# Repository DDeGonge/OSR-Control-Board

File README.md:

# OSR-Control-Board
Open Source Robotics Control Board - The cheap, overpowered, easy to use robotics controller.

## BOM
Latest BOM can be found [here](https://octopart.com/bom-tool/g8IoScnJ)

## Bootloader
Flashing instructions are found [here](https://learn.adafruit.com/how-to-program-samd-bootloaders/programming-the-bootloader-with-atmel-studio). Follow directions for Feather M4. Notch on flex cable faces AWAY from mcu.

## Random Stuff
Generate MD5 sum for packages - `CertUtil -hashfile C:\TEMP\MyDataFile.img MD5`

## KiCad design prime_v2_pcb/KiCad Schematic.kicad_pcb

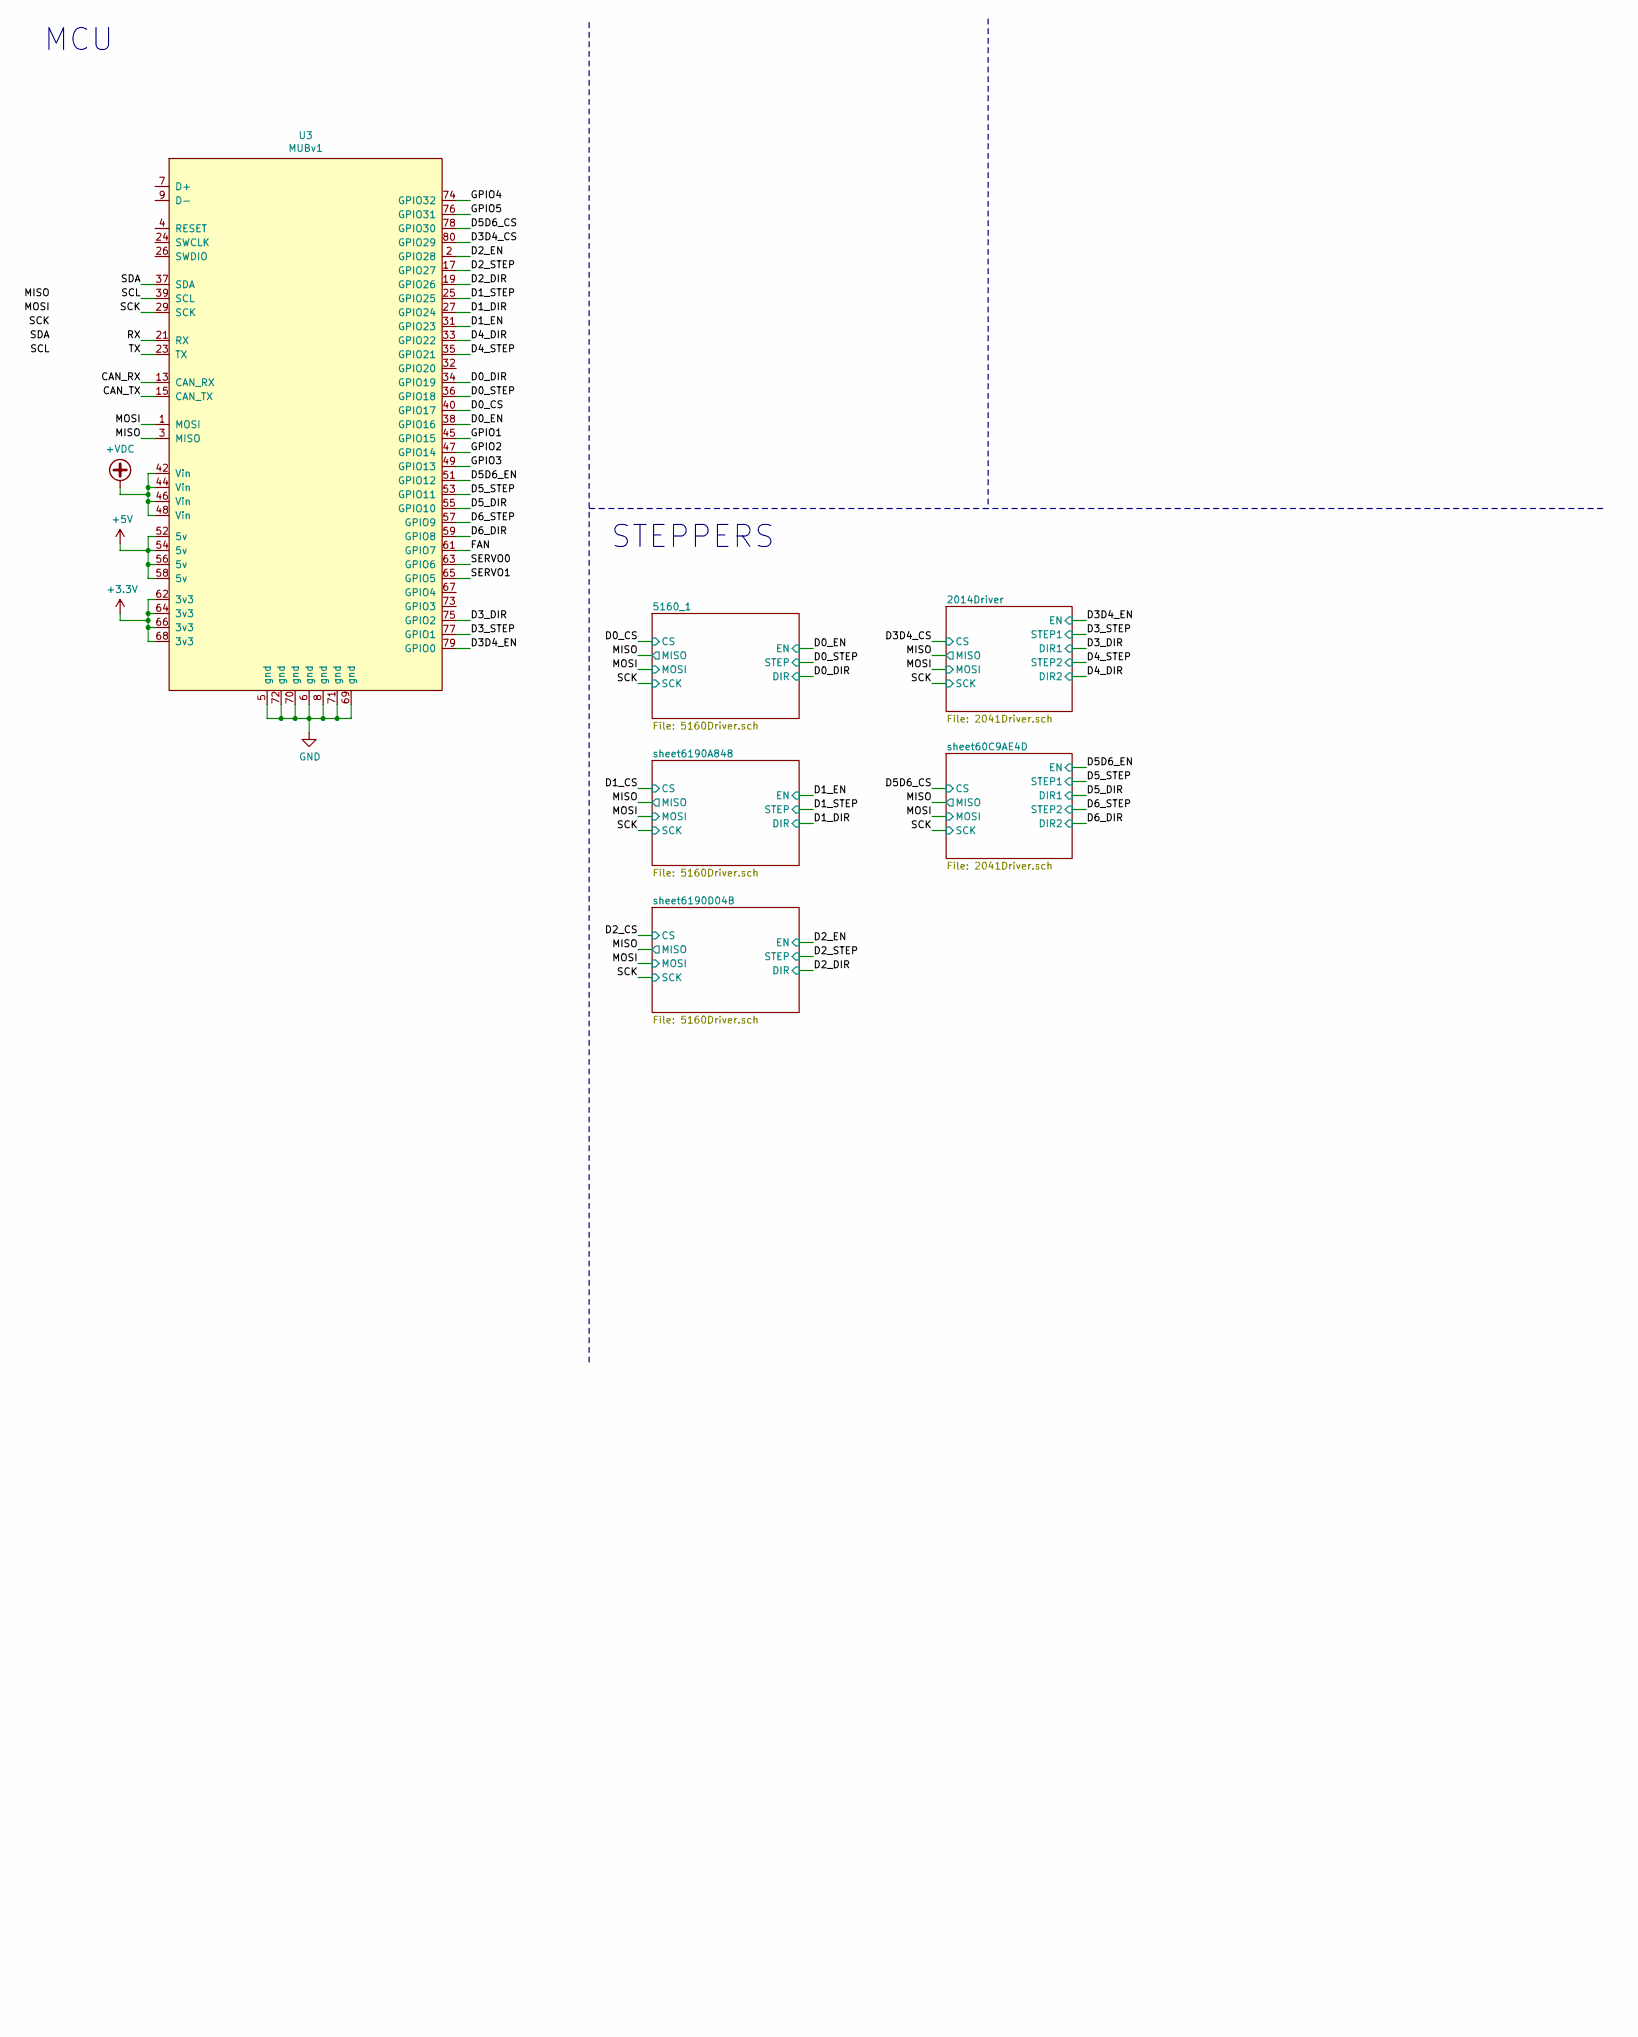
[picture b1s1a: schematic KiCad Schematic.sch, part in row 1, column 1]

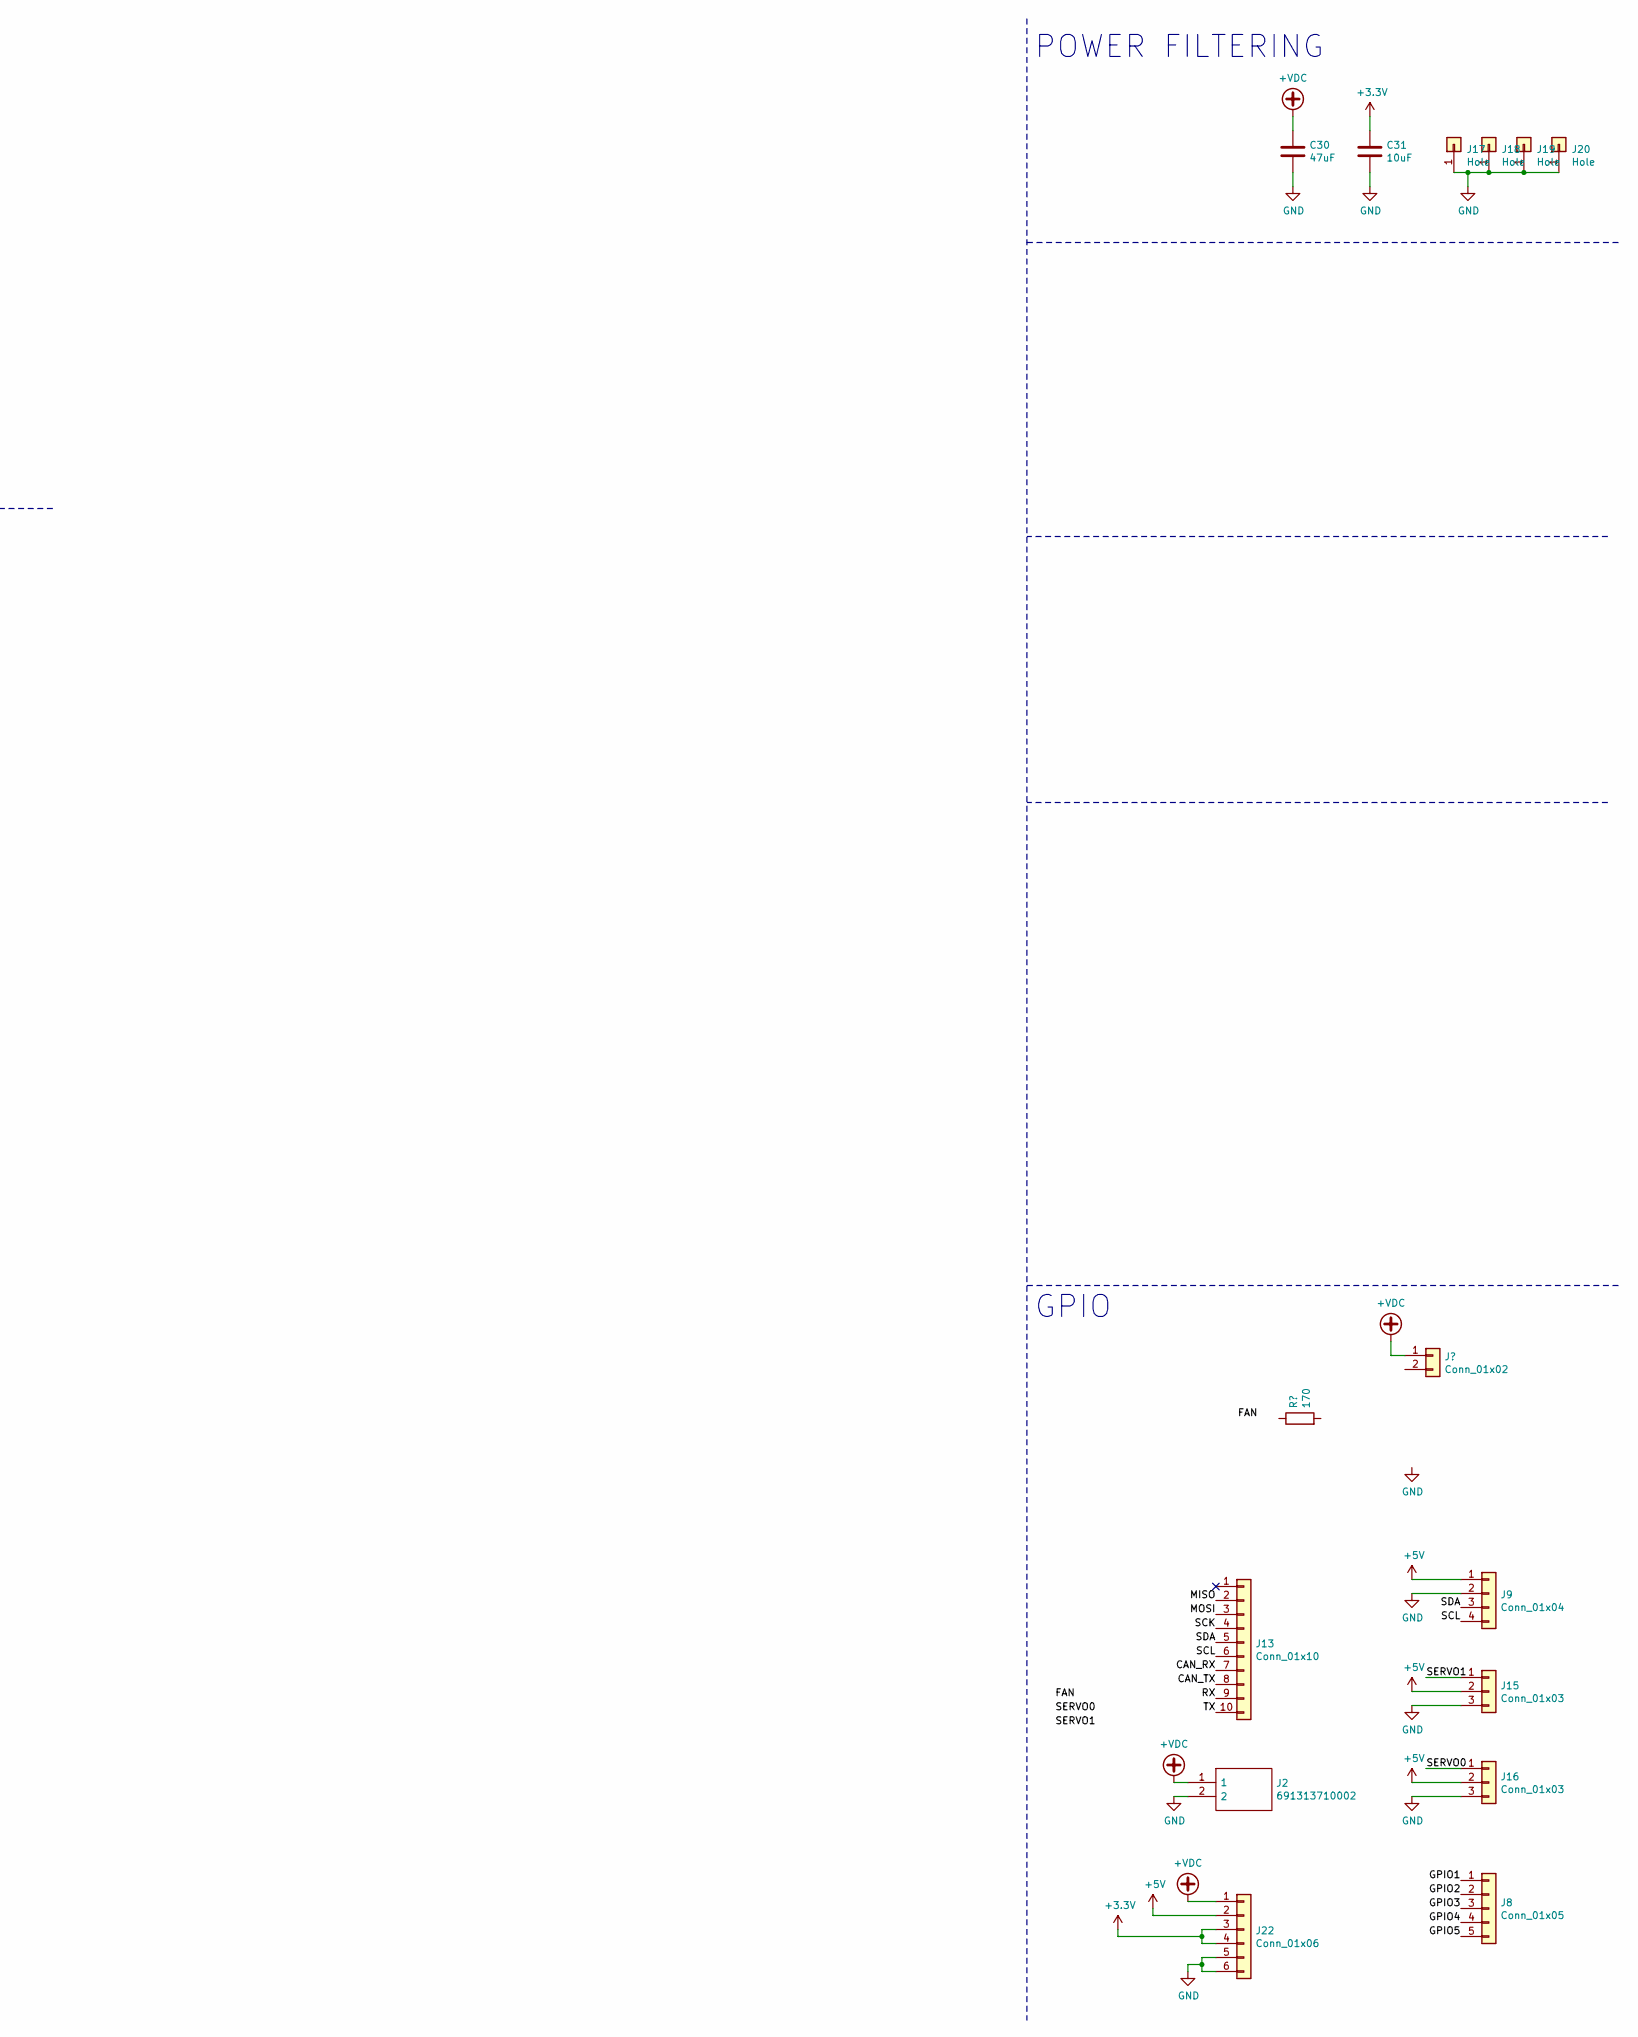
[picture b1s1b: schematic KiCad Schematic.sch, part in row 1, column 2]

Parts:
C30: 47uF; CP_Elec_6.3x7.7
C31: 10uF; C_0805_2012Metric
J2: 691313710002; Mouser Part Number 710-691313710002
J8: Conn_01x05; PinHeader_1x05_P2.54mm_Vertical
J9: Conn_01x04; PinHeader_1x04_P2.54mm_Vertical
J13: Conn_01x10; PinHeader_1x10_P2.54mm_Vertical
J15, J16: Conn_01x03; PinHeader_1x03_P2.54mm_Vertical
J17, J18, J19, J20: Hole; MountingHole_2.7mm_M2.5_DIN965_Pad
J22: Conn_01x06; PinSocket_1x06_P2.54mm_Vertical
U3: MUBv1; MUB_v1

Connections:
+5V: J9.1, J15.2, J16.2, J22.2, U3.52 (5v), U3.54 (5v), U3.56 (5v), U3.58 (5v)
+VDC: C30.1, J2.1, J22.1, U3.42 (Vin), U3.44 (Vin), U3.46 (Vin), U3.48 (Vin); also elsewhere on the board
/CAN_RX: J13.7, U3.13 (CAN_RX)
/CAN_TX: J13.8, U3.15 (CAN_TX)
/D0_CS: U3.40 (GPIO17); also elsewhere on the board
/D0_DIR: U3.34 (GPIO19); also elsewhere on the board
/D0_EN: U3.38 (GPIO16); also elsewhere on the board
/D0_STEP: U3.36 (GPIO18); also elsewhere on the board
/D1_DIR: U3.27 (GPIO24); also elsewhere on the board
/D1_EN: U3.31 (GPIO23); also elsewhere on the board
/D1_STEP: U3.25 (GPIO25); also elsewhere on the board
/D2_DIR: U3.19 (GPIO26); also elsewhere on the board
/D2_EN: U3.2 (GPIO28); also elsewhere on the board
/D2_STEP: U3.17 (GPIO27); also elsewhere on the board
/D3D4_CS: U3.80 (GPIO29); also elsewhere on the board
/D3D4_EN: U3.79 (GPIO0); also elsewhere on the board
/D3_DIR: U3.75 (GPIO2); also elsewhere on the board
/D3_STEP: U3.77 (GPIO1); also elsewhere on the board
/D4_DIR: U3.33 (GPIO22); also elsewhere on the board
/D4_STEP: U3.35 (GPIO21); also elsewhere on the board
/D5D6_CS: U3.78 (GPIO30); also elsewhere on the board
/D5D6_EN: U3.51 (GPIO12); also elsewhere on the board
/D5_DIR: U3.55 (GPIO10); also elsewhere on the board
/D5_STEP: U3.53 (GPIO11); also elsewhere on the board
/D6_DIR: U3.59 (GPIO8); also elsewhere on the board
/D6_STEP: U3.57 (GPIO9); also elsewhere on the board
/GPIO1: J8.1, U3.45 (GPIO15)
/GPIO2: J8.2, U3.47 (GPIO14)
/GPIO3: J8.3, U3.49 (GPIO13)
/GPIO4: J8.4, U3.74 (GPIO32)
/GPIO5: J8.5, U3.76 (GPIO31)
/MISO: J13.2, U3.3 (MISO); also elsewhere on the board
/MOSI: J13.3, U3.1 (MOSI); also elsewhere on the board
/RX: J13.9, U3.21 (RX)
/SCK: J13.4, U3.29 (SCK); also elsewhere on the board
/SCL: J9.4, J13.6, U3.39 (SCL)
/SDA: J9.3, J13.5, U3.37 (SDA)
/TX: J13.10, U3.23 (TX)
GND: C30.2, C31.2, J2.2, J9.2, J15.3, J16.3, J17.1, J18.1, J19.1, J20.1, J22.5, J22.6, U3.5 (gnd), U3.6 (gnd), U3.8 (gnd), U3.69 (gnd), U3.70 (gnd), U3.71 (gnd), U3.72 (gnd); also elsewhere on the board

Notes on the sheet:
GPIO
POWER FILTERING
MCU
STEPPERS

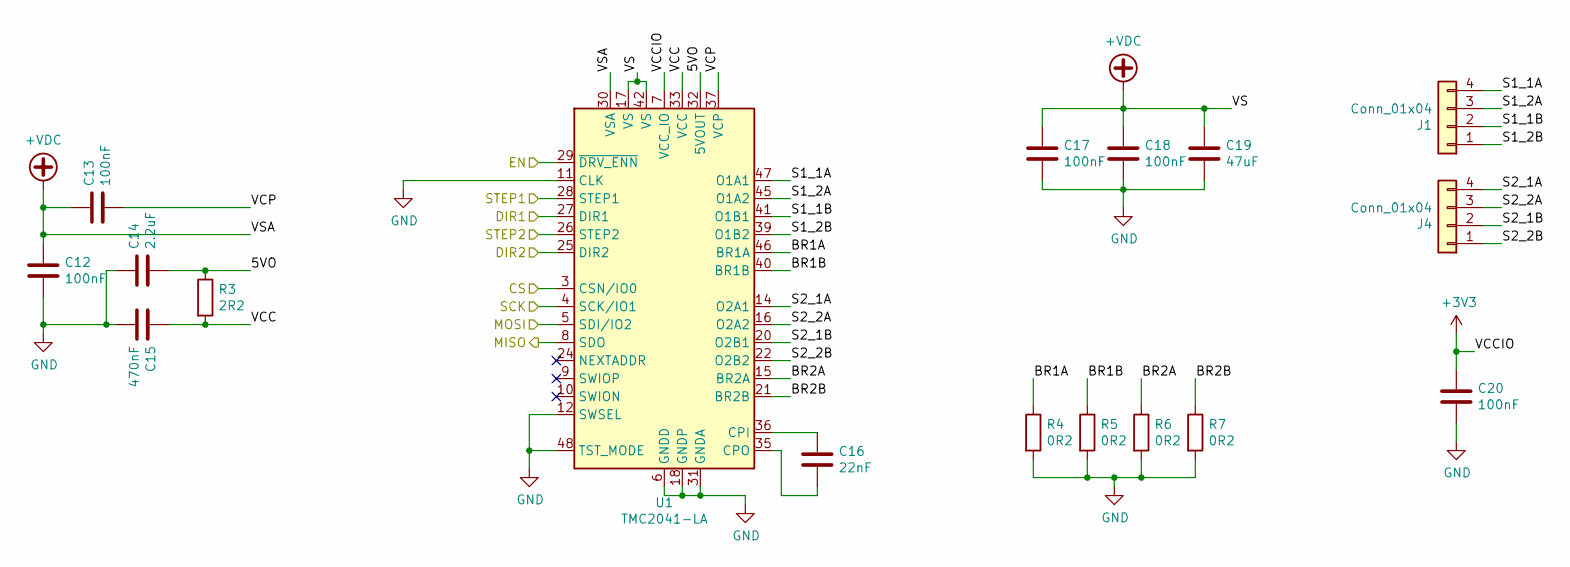
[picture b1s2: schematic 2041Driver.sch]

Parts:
C12, C13, C17, C18, C20: 100nF; C_0603_1608Metric
C14: 2.2uF; C_1206_3216Metric
C15: 470nF; C_0603_1608Metric
C16: 22nF; C_0603_1608Metric
C19: 47uF; CP_Elec_6.3x7.7
J1, J4: Conn_01x04; PinHeader_1x04_P2.54mm_Vertical
R3: 2R2; R_0603_1608Metric
R4, R5, R6, R7: 0R2; R_0805_2012Metric
U1: TMC2041-LA; QFN-48-1EP_7x7mm_P0.5mm_EP5.3x5.3mm

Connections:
+VDC: C12.1, C13.1, C17.1, C18.1, C19.1, U1.17 (VS), U1.19 (VS), U1.30 (VSA), U1.42 (VS), U1.44 (VS); also elsewhere on the board
/2014Driver/5VO: C14.2, R3.1, U1.32 (5VOUT)
/2014Driver/BR1A: R4.1, U1.46 (BR1A)
/2014Driver/BR1B: R5.1, U1.40 (BR1B)
/2014Driver/BR2A: R6.1, U1.15 (BR2A)
/2014Driver/BR2B: R7.1, U1.21 (BR2B)
/2014Driver/S1_1A: J1.4, U1.47 (O1A1)
/2014Driver/S1_1B: J1.2, U1.41 (O1B1)
/2014Driver/S1_2A: J1.3, U1.45 (O1A2)
/2014Driver/S1_2B: J1.1, U1.39 (O1B2)
/2014Driver/S2_1A: J4.4, U1.14 (O2A1)
/2014Driver/S2_1B: J4.2, U1.20 (O2B1)
/2014Driver/S2_2A: J4.3, U1.16 (O2A2)
/2014Driver/S2_2B: J4.1, U1.22 (O2B2)
/2014Driver/VCC: C15.1, R3.2, U1.33 (VCC)
/2014Driver/VCP: C13.2, U1.37 (VCP)
/D3D4_CS: U1.3 (CSN/IO0); also elsewhere on the board
/D3D4_EN: U1.29 (~DRV_ENN); also elsewhere on the board
/D3_DIR: U1.27 (DIR1); also elsewhere on the board
/D3_STEP: U1.28 (STEP1); also elsewhere on the board
/D4_DIR: U1.25 (DIR2); also elsewhere on the board
/D4_STEP: U1.26 (STEP2); also elsewhere on the board
/MISO: U1.8 (SDO); also elsewhere on the board
/MOSI: U1.5 (SDI/IO2); also elsewhere on the board
/SCK: U1.4 (SCK/IO1); also elsewhere on the board
GND: C12.2, C14.1, C15.2, C17.2, C18.2, C19.2, C20.2, R4.2, R5.2, R6.2, R7.2, U1.1 (GNDD), U1.2 (GNDD), U1.6 (GNDD), U1.11 (CLK), U1.12 (SWSEL), U1.13 (GNDD), U1.18 (GNDP), U1.23 (GNDD), U1.31 (GNDA), U1.34 (GNDD), U1.38 (GNDD), U1.43 (GNDP), U1.48 (TST_MODE), U1.49 (GNDD); also elsewhere on the board
unnamed: C16.1, U1.36 (CPI)
unnamed: C16.2, U1.35 (CPO)

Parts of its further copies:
C21, C22, C27, C42, C50: 100nF; C_0603_1608Metric
C23: 2.2uF; C_1206_3216Metric
C24: 470nF; C_0603_1608Metric
C26: 22nF; C_0603_1608Metric
C49: 47uF; CP_Elec_6.3x7.7
J5, J7: Conn_01x04; PinHeader_1x04_P2.54mm_Vertical
R8: 2R2; R_0603_1608Metric
R9, R10, R11, R12: 0R2; R_0805_2012Metric
U2: TMC2041-LA; QFN-48-1EP_7x7mm_P0.5mm_EP5.3x5.3mm

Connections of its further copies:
+VDC: C21.1, C22.1, C27.1, C42.1, C49.1, U2.17 (VS), U2.19 (VS), U2.30 (VSA), U2.42 (VS), U2.44 (VS); also elsewhere on the board
/D5D6_CS: U2.3 (CSN/IO0); also elsewhere on the board
/D5D6_EN: U2.29 (~DRV_ENN); also elsewhere on the board
/D5_DIR: U2.27 (DIR1); also elsewhere on the board
/D5_STEP: U2.28 (STEP1); also elsewhere on the board
/D6_DIR: U2.25 (DIR2); also elsewhere on the board
/D6_STEP: U2.26 (STEP2); also elsewhere on the board
/MISO: U2.8 (SDO); also elsewhere on the board
/MOSI: U2.5 (SDI/IO2); also elsewhere on the board
/SCK: U2.4 (SCK/IO1); also elsewhere on the board
/sheet60C9AE4D/5VO: C23.2, R8.1, U2.32 (5VOUT)
/sheet60C9AE4D/BR1A: R9.1, U2.46 (BR1A)
/sheet60C9AE4D/BR1B: R10.1, U2.40 (BR1B)
/sheet60C9AE4D/BR2A: R11.1, U2.15 (BR2A)
/sheet60C9AE4D/BR2B: R12.1, U2.21 (BR2B)
/sheet60C9AE4D/S1_1A: J5.4, U2.47 (O1A1)
/sheet60C9AE4D/S1_1B: J5.2, U2.41 (O1B1)
/sheet60C9AE4D/S1_2A: J5.3, U2.45 (O1A2)
/sheet60C9AE4D/S1_2B: J5.1, U2.39 (O1B2)
/sheet60C9AE4D/S2_1A: J7.4, U2.14 (O2A1)
/sheet60C9AE4D/S2_1B: J7.2, U2.20 (O2B1)
/sheet60C9AE4D/S2_2A: J7.3, U2.16 (O2A2)
/sheet60C9AE4D/S2_2B: J7.1, U2.22 (O2B2)
/sheet60C9AE4D/VCC: C24.1, R8.2, U2.33 (VCC)
/sheet60C9AE4D/VCP: C22.2, U2.37 (VCP)
GND: C21.2, C23.1, C24.2, C27.2, C42.2, C49.2, C50.2, R9.2, R10.2, R11.2, R12.2, U2.1 (GNDD), U2.2 (GNDD), U2.6 (GNDD), U2.11 (CLK), U2.12 (SWSEL), U2.13 (GNDD), U2.18 (GNDP), U2.23 (GNDD), U2.31 (GNDA), U2.34 (GNDD), U2.38 (GNDD), U2.43 (GNDP), U2.48 (TST_MODE), U2.49 (GNDD); also elsewhere on the board
unnamed: C26.1, U2.36 (CPI)
unnamed: C26.2, U2.35 (CPO)

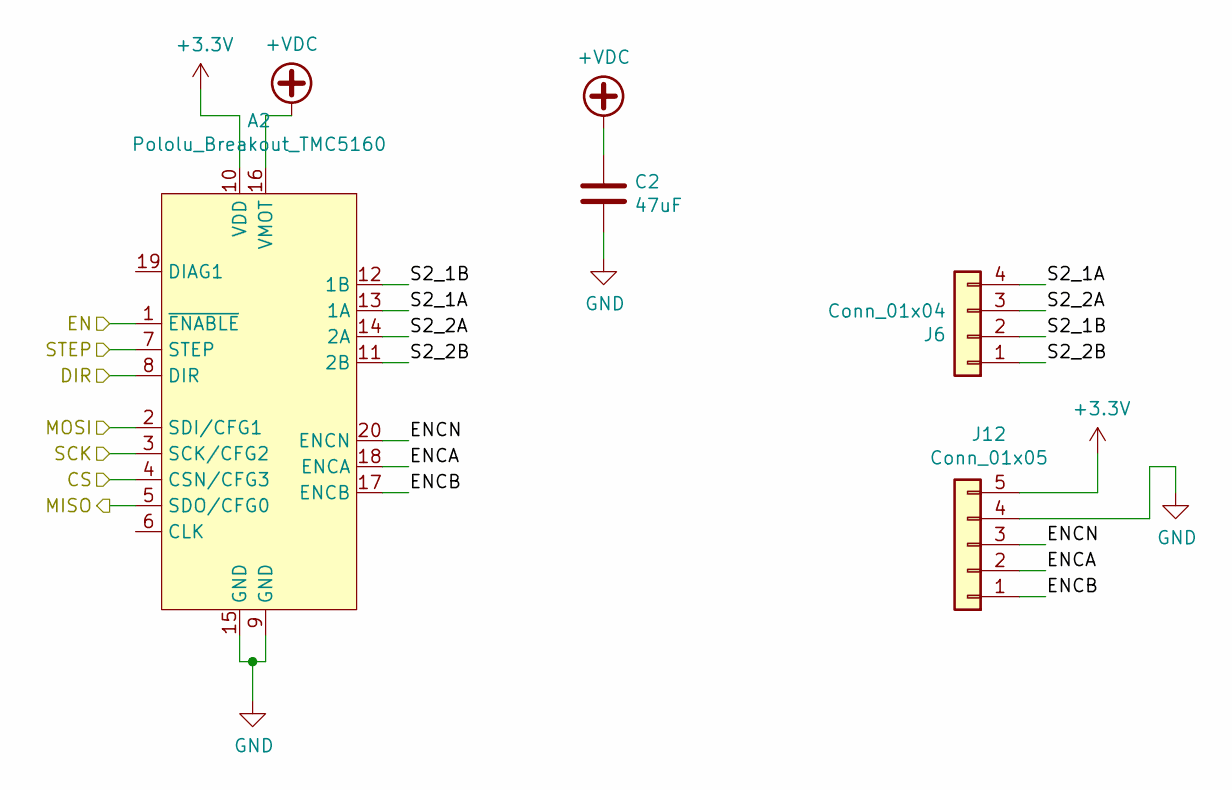
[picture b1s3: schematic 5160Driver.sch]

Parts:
A1: Pololu_Breakout_TMC5160; Pololu_Breakout-20_15.2x20.3mm
C1: 47uF; CP_Elec_6.3x7.7
J3: Conn_01x04; PinHeader_1x04_P2.54mm_Vertical
J11: Conn_01x05; PinHeader_1x05_P2.54mm_Vertical

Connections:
+VDC: A1.16 (VMOT), C1.1; also elsewhere on the board
/5160_1/ENCA: A1.18 (ENCA), J11.2
/5160_1/ENCB: A1.17 (ENCB), J11.1
/5160_1/ENCN: A1.20 (ENCN), J11.3
/5160_1/S2_1A: A1.13 (1A), J3.4
/5160_1/S2_1B: A1.12 (1B), J3.2
/5160_1/S2_2A: A1.14 (2A), J3.3
/5160_1/S2_2B: A1.11 (2B), J3.1
/D0_CS: A1.4 (CSN/CFG3); also elsewhere on the board
/D0_DIR: A1.8 (DIR); also elsewhere on the board
/D0_EN: A1.1 (~ENABLE); also elsewhere on the board
/D0_STEP: A1.7 (STEP); also elsewhere on the board
/MISO: A1.5 (SDO/CFG0); also elsewhere on the board
/MOSI: A1.2 (SDI/CFG1); also elsewhere on the board
/SCK: A1.3 (SCK/CFG2); also elsewhere on the board
GND: A1.9 (GND), A1.15 (GND), C1.2, J11.4; also elsewhere on the board

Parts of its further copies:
A2, A3: Pololu_Breakout_TMC5160; Pololu_Breakout-20_15.2x20.3mm
C2, C3: 47uF; CP_Elec_6.3x7.7
J6, J10: Conn_01x04; PinHeader_1x04_P2.54mm_Vertical
J12, J14: Conn_01x05; PinHeader_1x05_P2.54mm_Vertical

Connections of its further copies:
+VDC: A2.16 (VMOT), A3.16 (VMOT), C2.1, C3.1; also elsewhere on the board
/D1_CS: A2.4 (CSN/CFG3)
/D1_DIR: A2.8 (DIR); also elsewhere on the board
/D1_EN: A2.1 (~ENABLE); also elsewhere on the board
/D1_STEP: A2.7 (STEP); also elsewhere on the board
/D2_CS: A3.4 (CSN/CFG3)
/D2_DIR: A3.8 (DIR); also elsewhere on the board
/D2_EN: A3.1 (~ENABLE); also elsewhere on the board
/D2_STEP: A3.7 (STEP); also elsewhere on the board
/MISO: A2.5 (SDO/CFG0), A3.5 (SDO/CFG0); also elsewhere on the board
/MOSI: A2.2 (SDI/CFG1), A3.2 (SDI/CFG1); also elsewhere on the board
/SCK: A2.3 (SCK/CFG2), A3.3 (SCK/CFG2); also elsewhere on the board
/sheet6190A848/ENCA: A2.18 (ENCA), J12.2
/sheet6190A848/ENCB: A2.17 (ENCB), J12.1
/sheet6190A848/ENCN: A2.20 (ENCN), J12.3
/sheet6190A848/S2_1A: A2.13 (1A), J6.4
/sheet6190A848/S2_1B: A2.12 (1B), J6.2
/sheet6190A848/S2_2A: A2.14 (2A), J6.3
/sheet6190A848/S2_2B: A2.11 (2B), J6.1
/sheet6190D04B/ENCA: A3.18 (ENCA), J14.2
/sheet6190D04B/ENCB: A3.17 (ENCB), J14.1
/sheet6190D04B/ENCN: A3.20 (ENCN), J14.3
/sheet6190D04B/S2_1A: A3.13 (1A), J10.4
/sheet6190D04B/S2_1B: A3.12 (1B), J10.2
/sheet6190D04B/S2_2A: A3.14 (2A), J10.3
/sheet6190D04B/S2_2B: A3.11 (2B), J10.1
GND: A2.9 (GND), A2.15 (GND), A3.9 (GND), A3.15 (GND), C2.2, C3.2, J12.4, J14.4; also elsewhere on the board

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
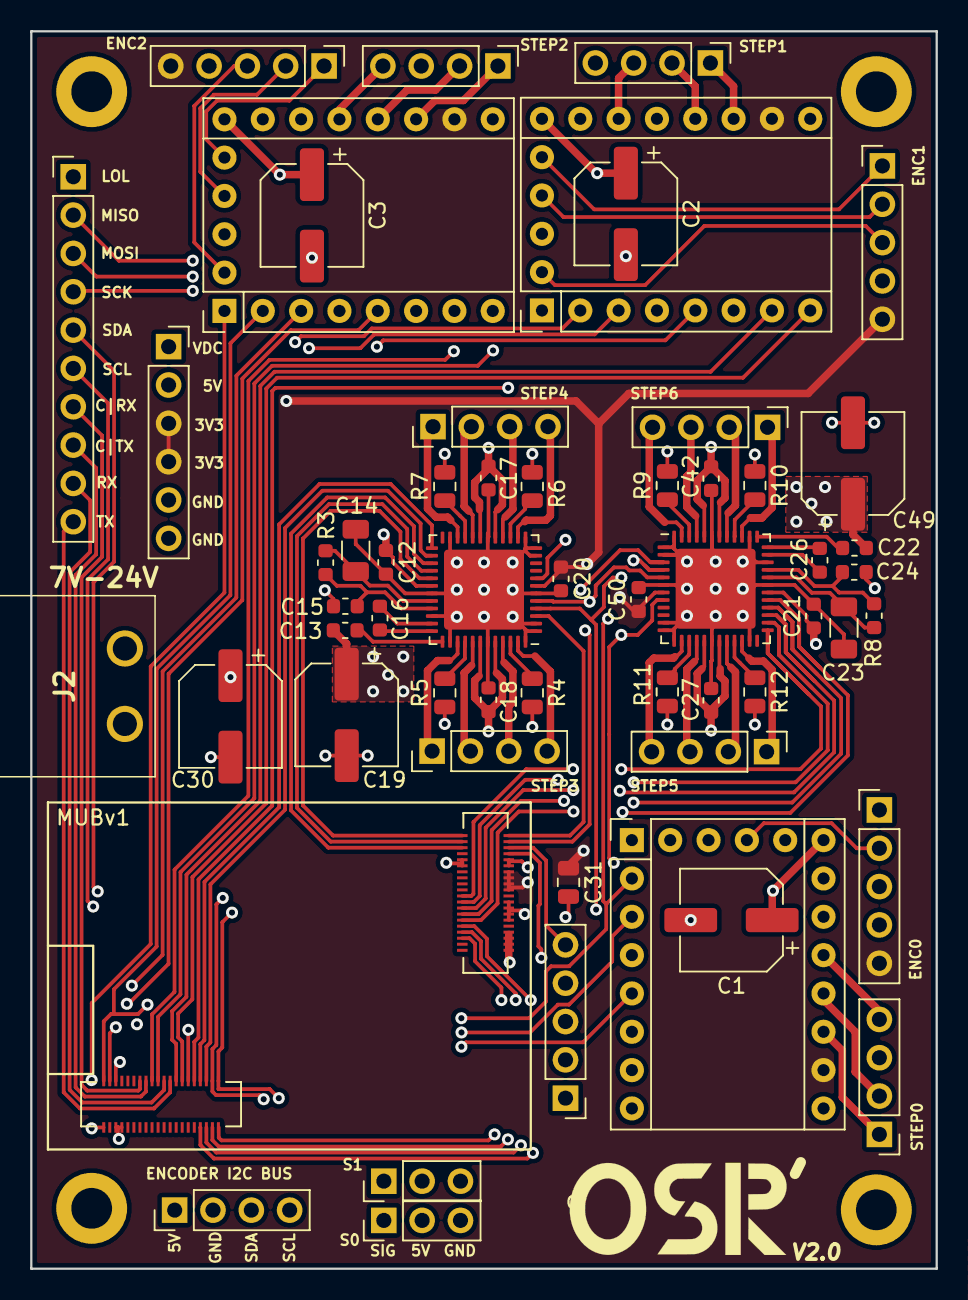
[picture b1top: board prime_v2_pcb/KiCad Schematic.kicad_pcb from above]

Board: 4 copper layers, 60.0 x 82.0 mm, 60 parts (0 on the bottom side), 95 nets.

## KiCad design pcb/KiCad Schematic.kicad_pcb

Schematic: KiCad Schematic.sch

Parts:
C1, C3, C5, C6, C7, C8, C9, C10, C11: 1uF; C_0603_1608Metric
C2, C31, C34, C35, C36: 10uF; C_0805_2012Metric
C4, C12, C13, C16, C18, C19, C21, C22, C25, C27, C28: 100nF; C_0603_1608Metric
C14, C23: 4.7uF; C_1206_3216Metric
C15, C24: 470nF; C_0603_1608Metric
C17, C26: 22nF; C_0603_1608Metric
C20, C29, C30: 47uF; CP_Elec_6.3x7.7
C32, C33: 22pF; C_0603_1608Metric
D1, D2: LED; LED_0603_1608Metric
D3, D4: CGRTS4004-HF; D_SOD-123F
IC1: AP63205WU-7; SOT95P280X100-6N; Mouser Part Number 621-AP63205WU-7
IC2: ATSAMD51J19A-MU; QFN-64-1EP_9x9mm_P0.5mm_EP6x6mm_ThermalVias; Mouser Part Number 556-ATSAMD51J19AMU
J1: 47571-0001; 475710001; Mouser Part Number 538-47571-0001
J2: Conn_01x02; BarrelJack_Wuerth_6941xx301002
J3: 47346-0001; Mouser Part Number 538-47346-0001
J4, J5, J10, J11: Conn_01x04; PinHeader_1x04_P2.54mm_Vertical
J6: 20021121-00010C4LF; 2002112100010C4LF; Mouser Part Number 649-202112100010C4LF
J7, J8, J9, J21: Conn_01x02; PinHeader_1x02_P2.54mm_Vertical
J12, J13, J15, J16: Conn_01x03; PinHeader_1x03_P2.54mm_Vertical
J14: Conn_01x20; PinSocket_1x20_P2.54mm_Vertical
J17, J18, J19, J20: Hole; MountingHole_2.7mm_M2.5_DIN965_Pad
J22: Conn_01x06; PinSocket_1x06_P2.54mm_Vertical
L1, L2, L3: 10uH; L_0805_2012Metric
Q1, Q2: NVTFS5C680NLTAG; NVTFS6H854NTAG; Mouser Part Number 863-NVTFS5C680NLTAG
R1, R2, R15, R16, R18, R22: 10k; R_0603_1608Metric
R3, R8: 2R2; R_0603_1608Metric
R4, R5, R6, R7, R9, R10, R11, R12: 0R2; R_0805_2012Metric
R13, R14, R17, R19, R20: 174; R_0603_1608Metric
R21: 100k; R_0603_1608Metric
S1: KMR243GLFG; KMR421GULCLFS; Mouser Part Number 611-KMR243GLFG
U1, U2: TMC2041-LA; QFN-48-1EP_7x7mm_P0.5mm_EP5.3x5.3mm_ThermalVias
U3: AP2112K-3.3; SOT-23-5
Y1: LFXTAL009678REEL; Mouser Part Number 449-LFXTAL009678REEL

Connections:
/AREF: C10.1, IC2.4 (PA03)
/D0_5VO: C14.2, R3.1, U2.32 (5VOUT)
/D0_CS: IC2.9 (PB06), U2.3 (CSN/IO0)
/D0_EN: IC2.59 (PB30), U2.29 (~DRV_ENN)
/D0_S0_1A: J10.1, U2.14 (O2A1)
/D0_S0_1B: J10.3, U2.20 (O2B1)
/D0_S0_2A: J10.2, U2.16 (O2A2)
/D0_S0_2B: J10.4, U2.22 (O2B2)
/D0_S0_DIR: IC2.61 (PB00), U2.27 (DIR1)
/D0_S0_STEP: IC2.60 (PB31), U2.28 (STEP1)
/D0_S1_1A: J11.1, U2.47 (O1A1)
/D0_S1_1B: J11.3, U2.41 (O1B1)
/D0_S1_2A: J11.2, U2.45 (O1A2)
/D0_S1_2B: J11.4, U2.39 (O1B2)
/D0_S1_DIR: IC2.5 (PB04), U2.25 (DIR2)
/D0_S1_STEP: IC2.6 (PB05), U2.26 (STEP2)
/D0_VCC: C15.1, R3.2, U2.33 (VCC)
/D0_VCP: C13.2, U2.37 (VCP)
/D1_5VO: C23.2, R8.1, U1.32 (5VOUT)
/D1_CS: IC2.37 (PA18), U1.3 (CSN/IO0)
/D1_EN: IC2.38 (PA19), U1.29 (~DRV_ENN)
/D1_S0_1A: J4.1, U1.14 (O2A1)
/D1_S0_1B: J4.3, U1.20 (O2B1)
/D1_S0_2A: J4.2, U1.16 (O2A2)
/D1_S0_2B: J4.4, U1.22 (O2B2)
/D1_S0_DIR: IC2.42 (PA21), U1.27 (DIR1)
/D1_S0_STEP: IC2.41 (PA20), U1.28 (STEP1)
/D1_S1_1A: J5.1, U1.47 (O1A1)
/D1_S1_1B: J5.3, U1.41 (O1B1)
/D1_S1_2A: J5.2, U1.45 (O1A2)
/D1_S1_2B: J5.4, U1.39 (O1B2)
/D1_S1_DIR: IC2.44 (PA23), U1.25 (DIR2)
/D1_S1_STEP: IC2.43 (PA22), U1.26 (STEP2)
/D1_VCC: C24.1, R8.2, U1.33 (VCC)
/D1_VCP: C22.2, U1.37 (VCP)
/D+: IC2.46 (PA25), J3.3 (D+)
/D-: IC2.45 (PA24), J3.2 (D-)
/GATE0: IC2.17 (PA08), J14.16, R13.2
/GATE1: IC2.18 (PA09), J14.17, R14.2
/GEN0: IC2.10 (PB07), J14.1
/GEN1: IC2.11 (PB08), J14.2
/GEN2: IC2.12 (PB09), J14.3
/GEN3: IC2.13 (PA04), J14.4
/GEN4: IC2.14 (PA05), J14.5
/GEN5: IC2.15 (PA06), J14.6
/GEN6: IC2.16 (PA07), J14.7
/GEN7: IC2.19 (PA10), J14.8
/GEN8: IC2.20 (PA11), J14.9
/GEN9: IC2.23 (PB10), J14.10
/GEN10: IC2.24 (PB11), J14.11
/GEN11: IC2.25 (PB12), J14.12
/GEN12: IC2.26 (PB13), J14.13
/GEN13: IC2.27 (PB14), J14.14
/GEN14: IC2.28 (PB15), J14.15, R20.2
/MISO: IC2.49 (PB22), J1.P7, J12.1, U1.8 (SDO), U2.8 (SDO)
/MOSI: IC2.50 (PB23), J1.P3, J12.2, U1.5 (SDI/IO2), U2.5 (SDI/IO2)
/OSC0: C32.2, IC2.1 (PA00), Y1.1 (CRYSTAL_1)
/OSC1: C33.1, IC2.2 (PA01), Y1.2 (CRYSTAL_2)
/RESET: C3.1, IC2.52 (RESETN), J6.10, R1.2, R19.2
/RX: IC2.40 (PB17), J21.2
/SCK: IC2.36 (PA17), J1.P5, J12.3, U1.4 (SCK/IO1), U2.4 (SCK/IO1)
/SCL: IC2.30 (PA13), J9.2, R18.2
/SDA: IC2.29 (PA12), J9.1, R16.2
/SD_CS: IC2.51 (PA27), J1.P2
/SERVO0: IC2.31 (PA14), J14.18, J16.1
/SERVO1: IC2.32 (PA15), J14.19, J15.1
/SERVO2: IC2.35 (PA16), J13.1, J14.20
/SWCLK: IC2.57 (PA30), J6.4, R15.2
/SWDIO: IC2.58 (PA31), J6.2
/TX: IC2.39 (PB16), J21.1
/VDDCORE: C1.1, C2.1, IC2.53 (VDDCORE), L1.2
/VSENSE: IC2.62 (PB01), R21.2, R22.1
/VSW: IC2.55 (VSW), L1.1
GND: C1.2, C2.2, C3.2, C5.2, C6.2, C7.2, C8.2, C9.2, C10.2, C11.2, C12.1, C14.1, C15.2, C16.1, C18.1, C19.1, C20.2, C21.1, C23.1, C24.2, C25.1, C27.1, C28.1, C29.2, C30.2, C31.2, C32.1, C33.2, C34.2, C35.2, C36.2, D1.1 (K), D2.1 (K), IC1.4 (GND), IC2.7 (GND_1), IC2.22 (GND_2), IC2.33 (GND_3), IC2.47 (GND_4), IC2.54 (GND_5), IC2.65 (EPAD), J1.G1, J1.G2, J1.G3, J1.P6, J2.2, J3.5 (GND), J6.3, J6.5, J13.3, J15.3, J16.3, J17.1, J18.1, J19.1, J20.1, J22.5, J22.6, Q1.1 (S_1), Q1.2 (S_2), Q1.3 (S_3), Q2.1 (S_1), Q2.2 (S_2), Q2.3 (S_3), R4.1, R5.1, R6.2, R7.2, R9.1, R10.1, R11.2, R12.2, R22.2, S1.2 (NO_1), S1.3 (NO_2), S1.5 (GND), U1.1 (GNDD), U1.2 (GNDD), U1.6 (GNDD), U1.11 (CLK), U1.12 (SWSEL), U1.13 (GNDD), U1.18 (GNDP), U1.23 (GNDD), U1.31 (GNDA), U1.34 (GNDD), U1.38 (GNDD), U1.43 (GNDP), U1.48 (TST_MODE), U1.49 (GNDD), U2.1 (GNDD), U2.2 (GNDD), U2.6 (GNDD), U2.11 (CLK), U2.12 (SWSEL), U2.13 (GNDD), U2.18 (GNDP), U2.23 (GNDD), U2.31 (GNDA), U2.34 (GNDD), U2.38 (GNDD), U2.43 (GNDP), U2.48 (TST_MODE), U2.49 (GNDD), U3.2 (GND)
unnamed: C4.1, IC1.5 (SW), L2.2, L3.2
unnamed: C4.2, IC1.6 (BST)
unnamed: C17.1, U2.36 (CPI)
unnamed: C17.2, U2.35 (CPO)
unnamed: C26.1, U1.36 (CPI)
unnamed: C26.2, U1.35 (CPO)
unnamed: D1.2 (A), R17.1
unnamed: D2.2 (A), R20.1
unnamed: D3.2 (A), J7.2, Q1.5 (D_1), Q1.6 (D_2), Q1.7 (D_3), Q1.8 (D_4)
unnamed: D4.2 (A), J8.2, Q2.5 (D_1), Q2.6 (D_2), Q2.7 (D_3), Q2.8 (D_4)
unnamed: Q1.4 (G), R13.1
unnamed: Q2.4 (G), R14.1
unnamed: R2.2, U3.3 (EN)
unnamed: R4.2, U2.40 (BR1B)
unnamed: R5.2, U2.21 (BR2B)
unnamed: R6.1, U2.46 (BR1A)
unnamed: R7.1, U2.15 (BR2A)
unnamed: R9.2, U1.40 (BR1B)
unnamed: R10.2, U1.21 (BR2B)
unnamed: R11.1, U1.46 (BR1A)
unnamed: R12.1, U1.15 (BR2A)
unnamed: R19.1, S1.1 (COM_1), S1.4 (COM_2)

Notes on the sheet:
GPIO
POWER REG
POWER FILTERING
STEPPERS 0/1
STEPPERS 2/3
COMS I/O
STATUS
FET GATES
PROG HEADER
MCU

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
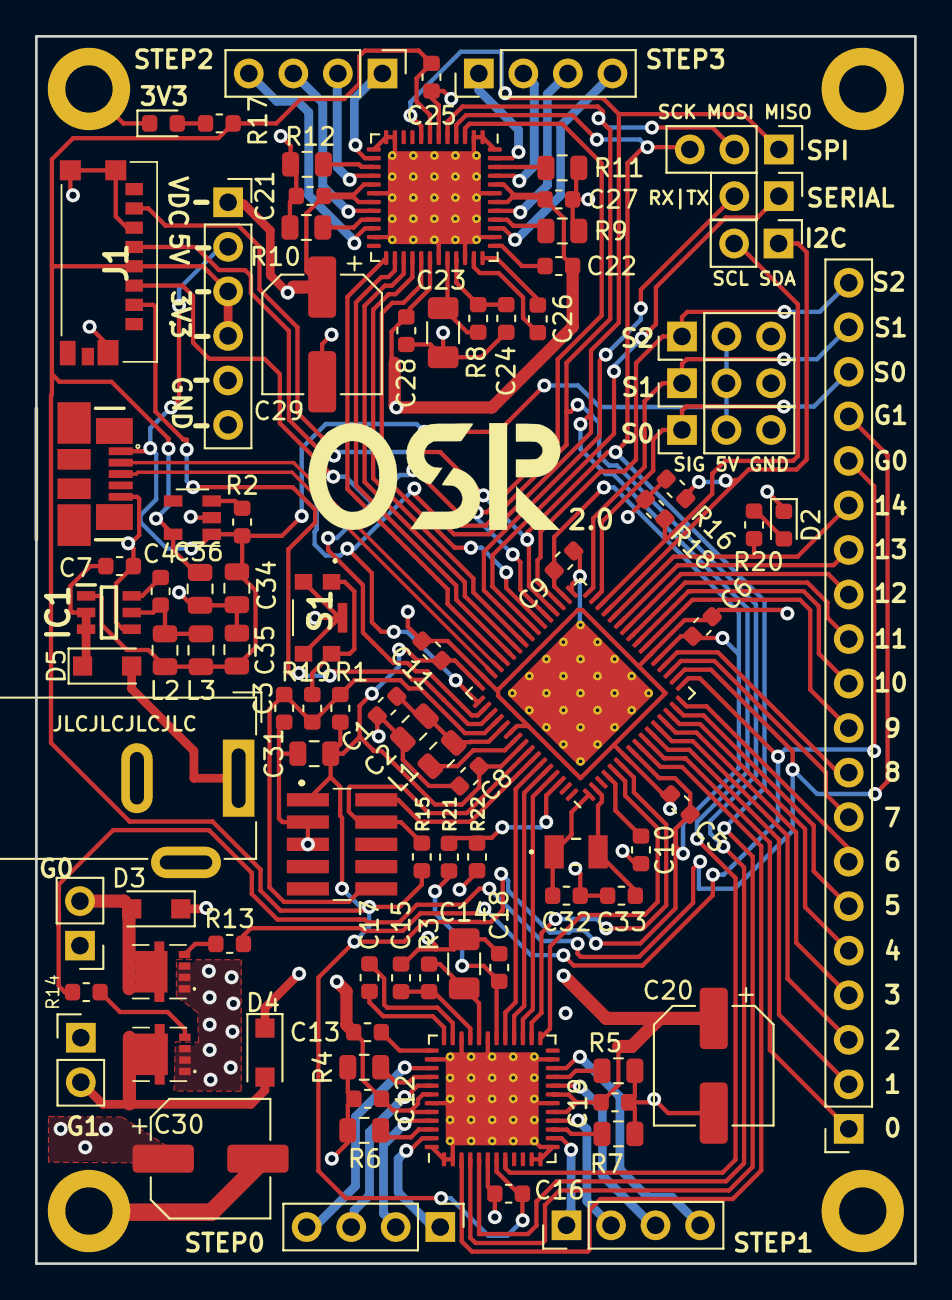
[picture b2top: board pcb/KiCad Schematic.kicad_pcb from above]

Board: 2 copper layers, 50.1 x 70.0 mm, 97 parts (0 on the bottom side), 100 nets.

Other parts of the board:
D5: CGRTS4004-HF; D_SOD-123F
